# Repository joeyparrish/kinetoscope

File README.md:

<h1>
  <picture>
    <source media="(prefers-color-scheme: dark)" srcset="logo-dark.svg">
    <source media="(prefers-color-scheme: light)" srcset="logo.svg">
    
  </picture>
</h1>

A Sega Genesis / Mega Drive Streaming Video Player

## Overview

Kinetoscope can either play video embedded in a standard ROM, or it can stream
video over WiFi using special hardware in a custom cartridge.  It uses a custom
video format detailed in
[`software/player/inc/segavideo_format.h`](software/player/inc/segavideo_format.h)
and encoded by
[`encoder/encode_sega_video.py`](encoder/encode_sega_video.py).

Kinetoscope takes its name from the [first moving picture
device](https://www.britannica.com/technology/Kinetoscope), invented in 1891 by
Thomas Edison and William Dickson.  While the 1891 original Kinetoscope was
able to display 46 frames per second, this project for a 1988 game console can
only push 10.

The default format is displayed at ~320x240p analog SD resolution at 10fps,
with 8-bit PCM audio at 13kHz.  The encoded pixels are not square.  The encoded
frames use a 256x224 resolution due to hardware limitations, and are displayed
at a different ratio by the Sega's Video Display Processor (VDP).

If video is embedded in the ROM, you can only fit about 13.6 seconds in a 4MB
cartridge/ROM.

For streaming, an RLE compression scheme is used to reduce required throughput,
and the microcontroller decompresses the video into SRAM on the fly.

Schematics and board layouts for special streaming hardware can be found in the
[`hardware/`](hardware/) folder.

You can download a pre-built emulator for macOS, Windows, or Linux from the
[releases page](https://github.com/joeyparrish/kinetoscope/releases).
(**NOTE:** On Linux, you should have OpenGL and PulseAudio pre-installed to use
these binaries.)

## Web Demo

To see Kinetoscope in a web-based emulator, check out
[https://joeyparrish.github.io/kinetoscope/](https://joeyparrish.github.io/kinetoscope/)

## Prototype

The first working prototype of the hardware was a stack of boards that looked
like this:

## Presentation

 - [Video presentation](https://youtu.be/0Atlf_whVgA)
 - [Presentation slides](https://docs.google.com/presentation/d/1nqJEwOmjEmVEMR6anbMV5HIaqYFpPi18ib-LaNSrTQE/)

## Project Folders

Each folder has a README with more information, including prerequisites that
must be installed to work on that part of the project.

 - [`software/`](software/): The player library and sample projects, which run
   on the Sega, written using [SGDK][].
 - [`encoder/`](encoder/): The video encoder, which generates videos in an
   appropriate format for embedding or streaming.
 - [`hardware/`](hardware/): The schematics and board layouts for a custom
   cartridge with special streaming hardware.
 - [`firmware/`](firmware/): The firmware that runs on the microcontroller of
   the custom cartridge hardware.
 - [`emulator-patches/`](emulator-patches/): Patches for OSS emulators to
   emulate the streaming hardware.
 - [`server/`](server/): Details on running a server for Sega video streams.
 - [`canned-videos/`](canned-videos/): Download canned, pre-encoded videos.

## Links

Related Projects:

 - [SGDK][]: A free and open development kit for the Sega Genesis / Mega Drive
 - The logo font is [Kode Mono](https://kodemono.com/)
 - [Sega Genesis Slide Generator and Viewer](https://github.com/joeyparrish/sega-slides/)
 - [Krikzz](https://krikzz.com/our-products/cartridges/): Incredible hardware
   for retro game console hacking and development, including flash carts

Socials:

 - [LinkedIn](https://www.linkedin.com/in/joeyparrish/)
 - [Video-Dev Slack](https://www.video-dev.org/)
 - [Pokemon Go](https://joeyparrish.github.io/joeyparrish/logos/trainer-code.png)
 - End of list

[SGDK]: https://github.com/Stephane-D/SGDK

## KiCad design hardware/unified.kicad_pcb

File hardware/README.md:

# Kinetoscope Hardware Design

The hardware is composed of several stacking boards, each of which hosts a set
of subcomponents.  The subcomponents are each in a subsheet, exposing
hierarchical pins and buses to the parent sheet.

One of these boards includes a microcontroller with WiFi, and runs its own
firmware to take commands from the Sega ROM.  See firmware in the
`../firmware/` folder.

## Prototype

The first working prototype looked like this:

## Prerequisites

The hardware design was done in KiCad 9, and routing was done in FreeRouting.
To install KiCad 9 and FreeRouting on Ubuntu, run:

```sh
sudo add-apt-repository --yes ppa:kicad/kicad-9.0-releases
sudo apt update
sudo apt install --install-recommends kicad default-jre wget unzip
wget https://github.com/freerouting/freerouting/releases/download/v1.9.0/freerouting-1.9.0-linux-x64.zip
sudo unzip -j -d /opt/freerouting freerouting-1.9.0-linux-x64.zip freerouting-1.9.0-linux-x64/lib/app/freerouting-executable.jar
```

To see hardware schematics without KiCad, open the PDF files in the
[`hardware/`](hardware/) folder.

To order boards, see hardware zip files attached to
[releases](https://github.com/joeyparrish/kinetoscope/releases).  These can be
uploaded to JLCPCB.

TODO: Document ordering process

## Boards

The stacking boards are:
 - `cart`: Cartridge Board
   - This is the board that actually plugs into the Sega Genesis.
   - It has 2MB of flash, which acts as the "ROM" chip for addresses 0-2MB, and
     contains the code that runs on the Sega.
   - The flash chip is compatible with the [Krikzz FlashKit Programmer MD][].
   - There is also a pin header on top that the other boards stack onto.
   - The pin header could also be used as a kind of breakout board for the
     development of other Sega cartridge projects.
   - Right-angle pin headers on the sides of the board are optional, and used
     only for debugging.
   - When ordering this through JLCPCB:
     - Be sure to set the following options:
       - Surface Finish: ENIG
       - Gold Fingers: Yes
       - 30°finger chamfered: Yes
     - The following parts will not be properly placed by JLCPCB's systems
       automatically, and must be adjusted manually during the ordering process:
       - J1 (pin header for attaching other boards, wrong location and rotation)
       - U2 (voltage regulator, offset a little too far to the right)
     - The following optional parts _may_ be populated by hand if you wish:
       - J4 (2-pin right-angle header for measuring current)
 - `sram-bank`: SRAM Bank Board
   - There are actually two of these in the stack, one for each 1MB SRAM bank.
   - These host the SRAM itself, and the buffers that allow it to be
     alternately controlled by the Sega or the microcontroller.  This is the
     most complex.  Two solder jumpers on the board select whether it responds
     as bank 0 or bank 1.
   - When ordering this through JLCPCB:
     - The following parts could easily be populated by hand if you wish:
       - J1 & J2 (stacking headers, 2x26 and 2x21 pins respectively)
     - The following **must** be soldered by hand:
       - JP1 and JP2 are solder jumpers that must be closed on each board; to
         set bank 0, bridge center to left on both jumpers; to set bank 1,
         bridge center to right on both jumpers (also indicated on silkscreen)
 - `microcontroller`: Microcontroller Board
   - This hosts the microcontroller, registers, sync token, and buffers to send
     data to SRAM.
   - The registers and sync token allow the Sega to send commands to the
     microcontroller and wait for responses.
   - The microcontroller is a Raspberry Pi Pico W, which receives commands
     through the registers and sync token, and is responsible for WiFi/Ethernet
     and streaming video to SRAM.  You can buy one here for $7 (as of September
     2024): https://www.adafruit.com/product/5544
   - When ordering this through JLCPCB:
     - The following parts may not be properly rendered by JLCPCB's systems
       automatically.  You may choose to leave them off your order and populate
       them by hand if you wish:
       - J3 and J4 are 20-pin female headers @ 0.1 inch pitch, to mount a
         Raspberry Pi Pico W with male headers facing down
     - The following parts could easily be populated by hand if you wish:
       - J1 & J2 (stacking headers, 2x26 and 2x21 pins respectively)
       - J6 (optional 2x3 female header to connect to an Ethernet Adapter Board
         with an [Adafruit Ethernet Featherwing][])
     - The following **must** be done by hand:
       - A single jumper must be added to either J5 or J7 (see silkscreen notes
         for play vs programming setting)
 - `ethernet`: Ethernet Adapter Board
   - This connects to an optional header on the microcontroller board and
     allows you to plug in the [Adafruit Ethernet Featherwing][].
   - If Ethernet is connected, the firmware prefers Ethernet over WiFi.
   - When ordering this through JLCPCB:
     - All headers could easily be populated by hand if you wish to skip paid
       assembly:
       - J1 & J2 (female headers on top of the board, 1x16 and 1x12
         respectively, where the Featherwing plugs in)
     - The following **must** be done by hand, because JLCPCB will only
       populate one side of the board:
       - J3 (male header on the bottom of the board, where it attaches to the
         Microcontroller Board)

## Sheets

The subsheets are:
 - `address-counter-internal`: SRAM address counter
   - The microcontroller doesn't have enough pins to output the SRAM address it
     wants to write to, so instead, this counter is used to generate sequential
     addresses.
 - `buffer-16-internal`: 16-bit tri-state, level-shifting buffer
   - This buffer allows us to manage control of the 16-bit data bus on the
     SRAM, switching between Sega and microcontroller control when needed.
 - `buffer-22-internal`: 22-bit tri-state, level-shifting buffer
   - This buffer allows us to manage control of the 19-bit address bus and
     control signals on the SRAM, switching between Sega and microcontroller
     control when needed.
 - `data-register-internal`: 16-bit serial-to-parallel shift register
   - The microcontroller doesn't have enough pins to output the SRAM words it
     wants to write, so instead, this register is used to convert a serial
     output from the microcontroller into the parallel input needed by the
     SRAM.
 - `flash-internal`: Flash connected to buses
   - Flash memory connected to buses to simplify top-level schematics.
 - `kinetoscope-header-internal`: Kinetoscope stacking pin headers
   - The stacking pin headers used for inter-board signals.
 - `register-file-internal`: 4x 8-bit Register File
   - Special registers the Sega writes to and the microcontroller reads from to
     receive commands.
 - `sram-internal`: SRAM connected to buses
   - SRAM connected to buses to simplify top-level schematics.
 - `sync-token-internal`: Shared Sync Token
   - A pair of single bit tokens.  One can be set by the Sega and cleared by
     the microcontroller, and the other vice-versa.  Both CPUs can read the
     state of both tokens.  For the command bit, the Sega sets it to tell the
     microcontroller that a command has been written to the registers. The
     microcontroller clears it when the command has been completed.  For the
     error bit, the microcontroller sets it to tell the Sega that an error has
     occurred, and the Sega clears it after the error has been read.

## Routing

To reroute a PCB after modifying the schematic:

  1. Open the PCB in KiCad
  2. Select all (CTRL+A)
  3. Right click the board, "Select >", "Filter Selected Items..."
  4. Uncheck "All items"
  5. Check "Include tracks" and "Include vias"
  6. Delete (Delete key)
  7. Update PCB from schematic (F8)
  8. Click "Update PCB", then "Close"
  9. Save PCB (CTRL+S)
  10. Select "File", "Export >", "Specctra DSN..."
  11. Click "Save" (and "Replace" if prompted)
  12. Run `route-pcb.sh` with the name of the board.  For example:

```sh
./route-pcb.sh sram-bank
```

After the routing process completes:

  1. Open the PCB in KiCad
  2. Select "File", "Import >", "Specctra Session..."
  3. Select the .ses file corresponding to this design
  4. Click "Open"
  5. Redo fill zones (B)
  6. Select "Inspect", "Design Rules Checker"
  7. Click "Run DRC"
  8. Manually fix any violations or unconnected items

## Programming

To program the Flash chip in-place:
 1. Insert the cartridge board into the [Krikzz FlashKit Programmer MD][]
 2. Write to it as you would a normal flash cart, using the
    [original FlashKit-MD software][] (GUI) or [FlashKit MD Python Client][]
    (command line)

[Krikzz FlashKit Programmer MD]: https://krikzz.com/our-products/accessories/flashkitmd.html
[original FlashKit-MD software]: https://krikzz.com/pub/support/flashkit-md/
[FlashKit MD Python Client]: https://github.com/joeyparrish/flashkit-md-py
[Adafruit Ethernet Featherwing]: https://www.adafruit.com/product/3201

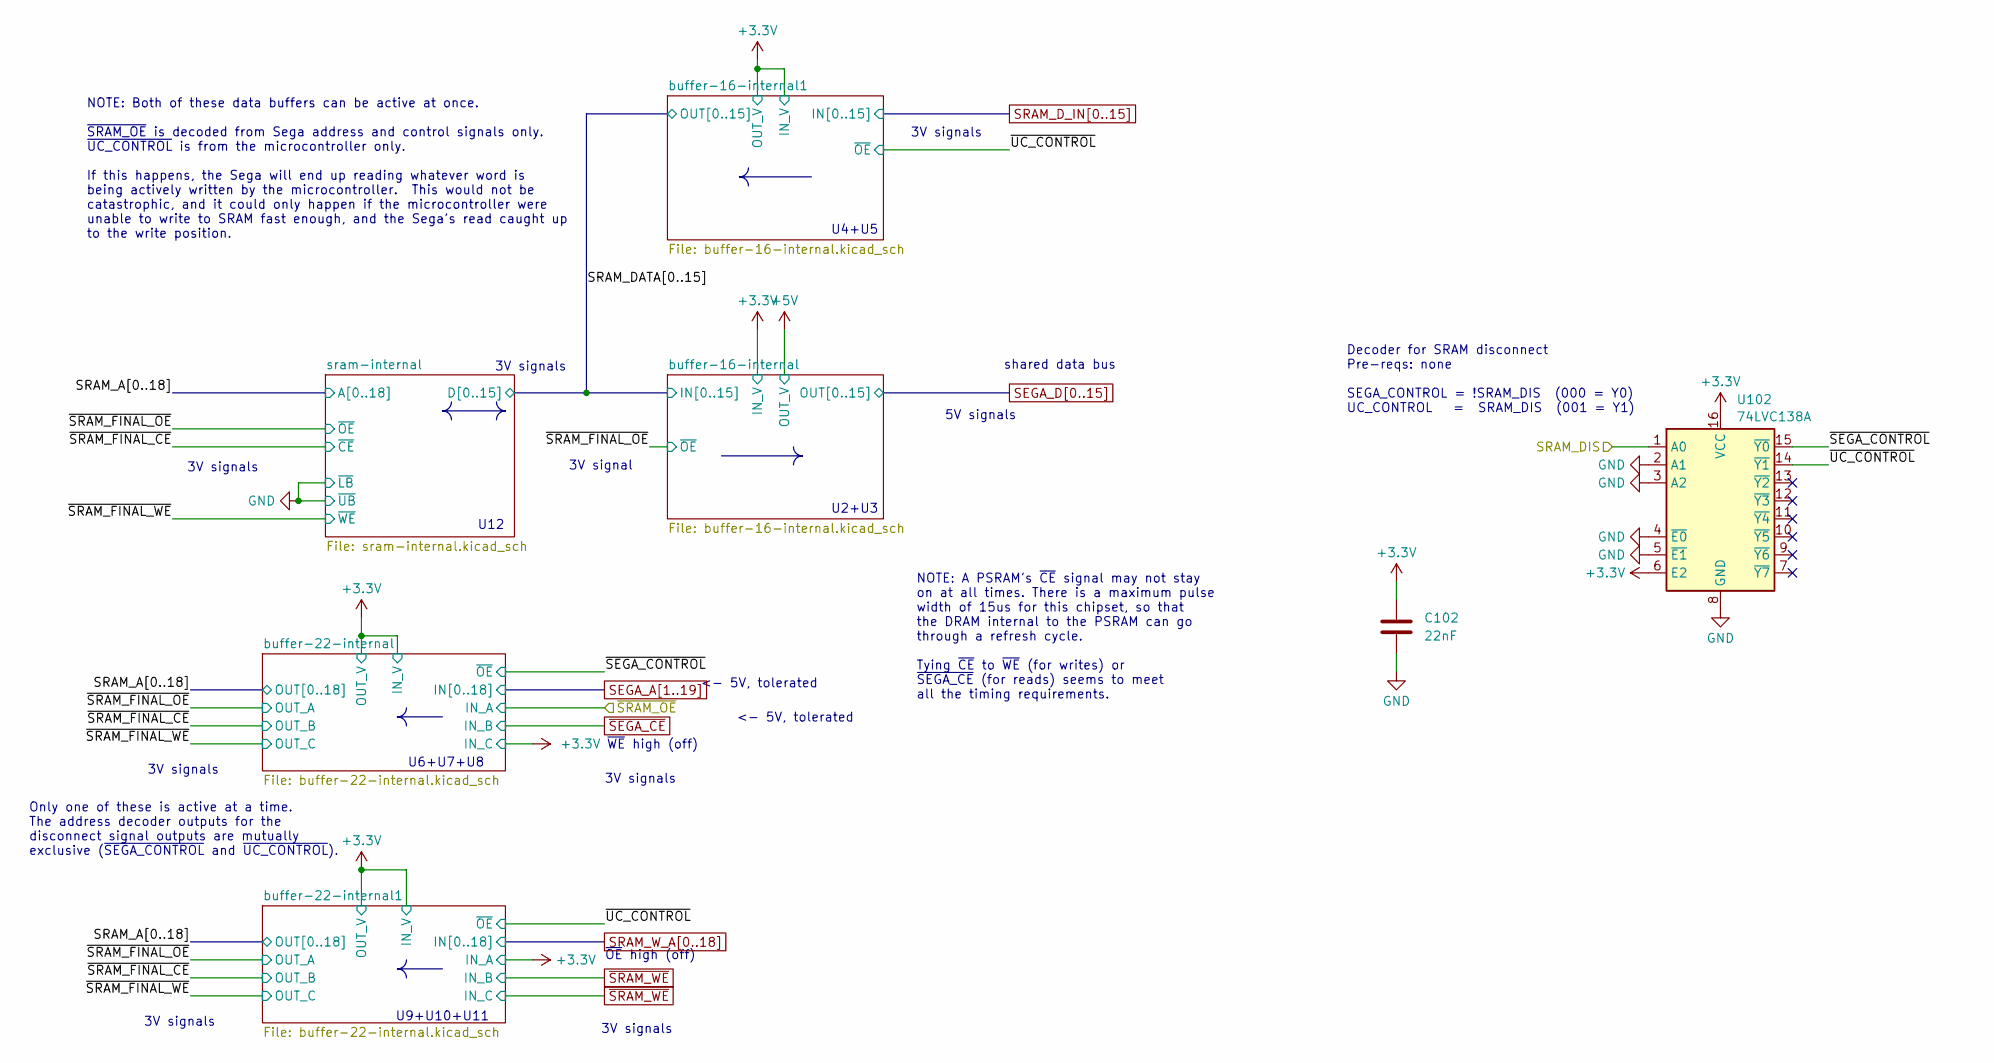
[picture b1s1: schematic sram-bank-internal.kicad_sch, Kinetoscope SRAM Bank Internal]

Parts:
C102: 22nF; C_0603_1608Metric; Mouser Part Number 80-C0603C223K4R; JLCPCB Part Number CL10B223KB8NNNC
U102: 74LVC138A; TSSOP-16_4.4x5mm_P0.65mm; Mouser Part Number 771-74LVC138APW-T; JLCPCB Part Number C6062

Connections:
+3.3V: C102.1, U102.6 (E2), U102.16 (VCC); also elsewhere on the board
/sram-bank-internal/~SEGA_CONTROL: U102.15 (~Y0); also elsewhere on the board
/sram-bank-internal/~UC_CONTROL: U102.14 (~Y1); also elsewhere on the board
GND: C102.2, U102.2 (A1), U102.3 (A2), U102.4 (~E0), U102.5 (~E1), U102.8 (GND); also elsewhere on the board
SRAM_DIS_0: U102.1 (A0); also elsewhere on the board

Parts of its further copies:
C201: 22nF; C_0603_1608Metric; Mouser Part Number 80-C0603C223K4R; JLCPCB Part Number CL10B223KB8NNNC
U201: 74LVC138A; TSSOP-16_4.4x5mm_P0.65mm; Mouser Part Number 771-74LVC138APW-T; JLCPCB Part Number C6062

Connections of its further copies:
+3.3V: C201.1, U201.6 (E2), U201.16 (VCC); also elsewhere on the board
/sram-bank-internal1/~SEGA_CONTROL: U201.15 (~Y0); also elsewhere on the board
/sram-bank-internal1/~UC_CONTROL: U201.14 (~Y1); also elsewhere on the board
GND: C201.2, U201.2 (A1), U201.3 (A2), U201.4 (~E0), U201.5 (~E1), U201.8 (GND); also elsewhere on the board
SRAM_DIS_1: U201.1 (A0); also elsewhere on the board

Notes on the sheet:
5V signals
U6+U7+U8
3V signals
U9+U10+U11
<- 5V, tolerated
U4+U5
U12
shared data bus
3V signal
Decoder for SRAM disconnect Pre-reqs: none SEGA_CONTROL = !SRAM_DIS (000 = Y0) UC_CONTROL = SRAM_DIS (001 = Y1)
NOTE: A PSRAM's ~{CE} signal may not stay on at all times. There is a maximum pulse width of 15us for this chipset, so that the DRAM internal to the PSRAM can go through a refresh cycle. Tying ~{CE} to ~{WE} (for writes) or ~{SEGA_CE} (for reads) seems to meet all the timing requirements.
~{OE} high (off)
U2+U3
Only one of these is active at a time. The address decoder outputs for the disconnect signal outputs are mutually exclusive (~{SEGA_CONTROL} and ~{UC_CONTROL}).
~{WE} high (off)
NOTE: Both of these data buffers can be active at once. ~{SRAM_OE} is decoded from Sega address and control signals only. ~{UC_CONTROL} is from the microcontroller only. If this happens, the Sega will end up reading whatever word is being actively written by the microcontroller. This would not be c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

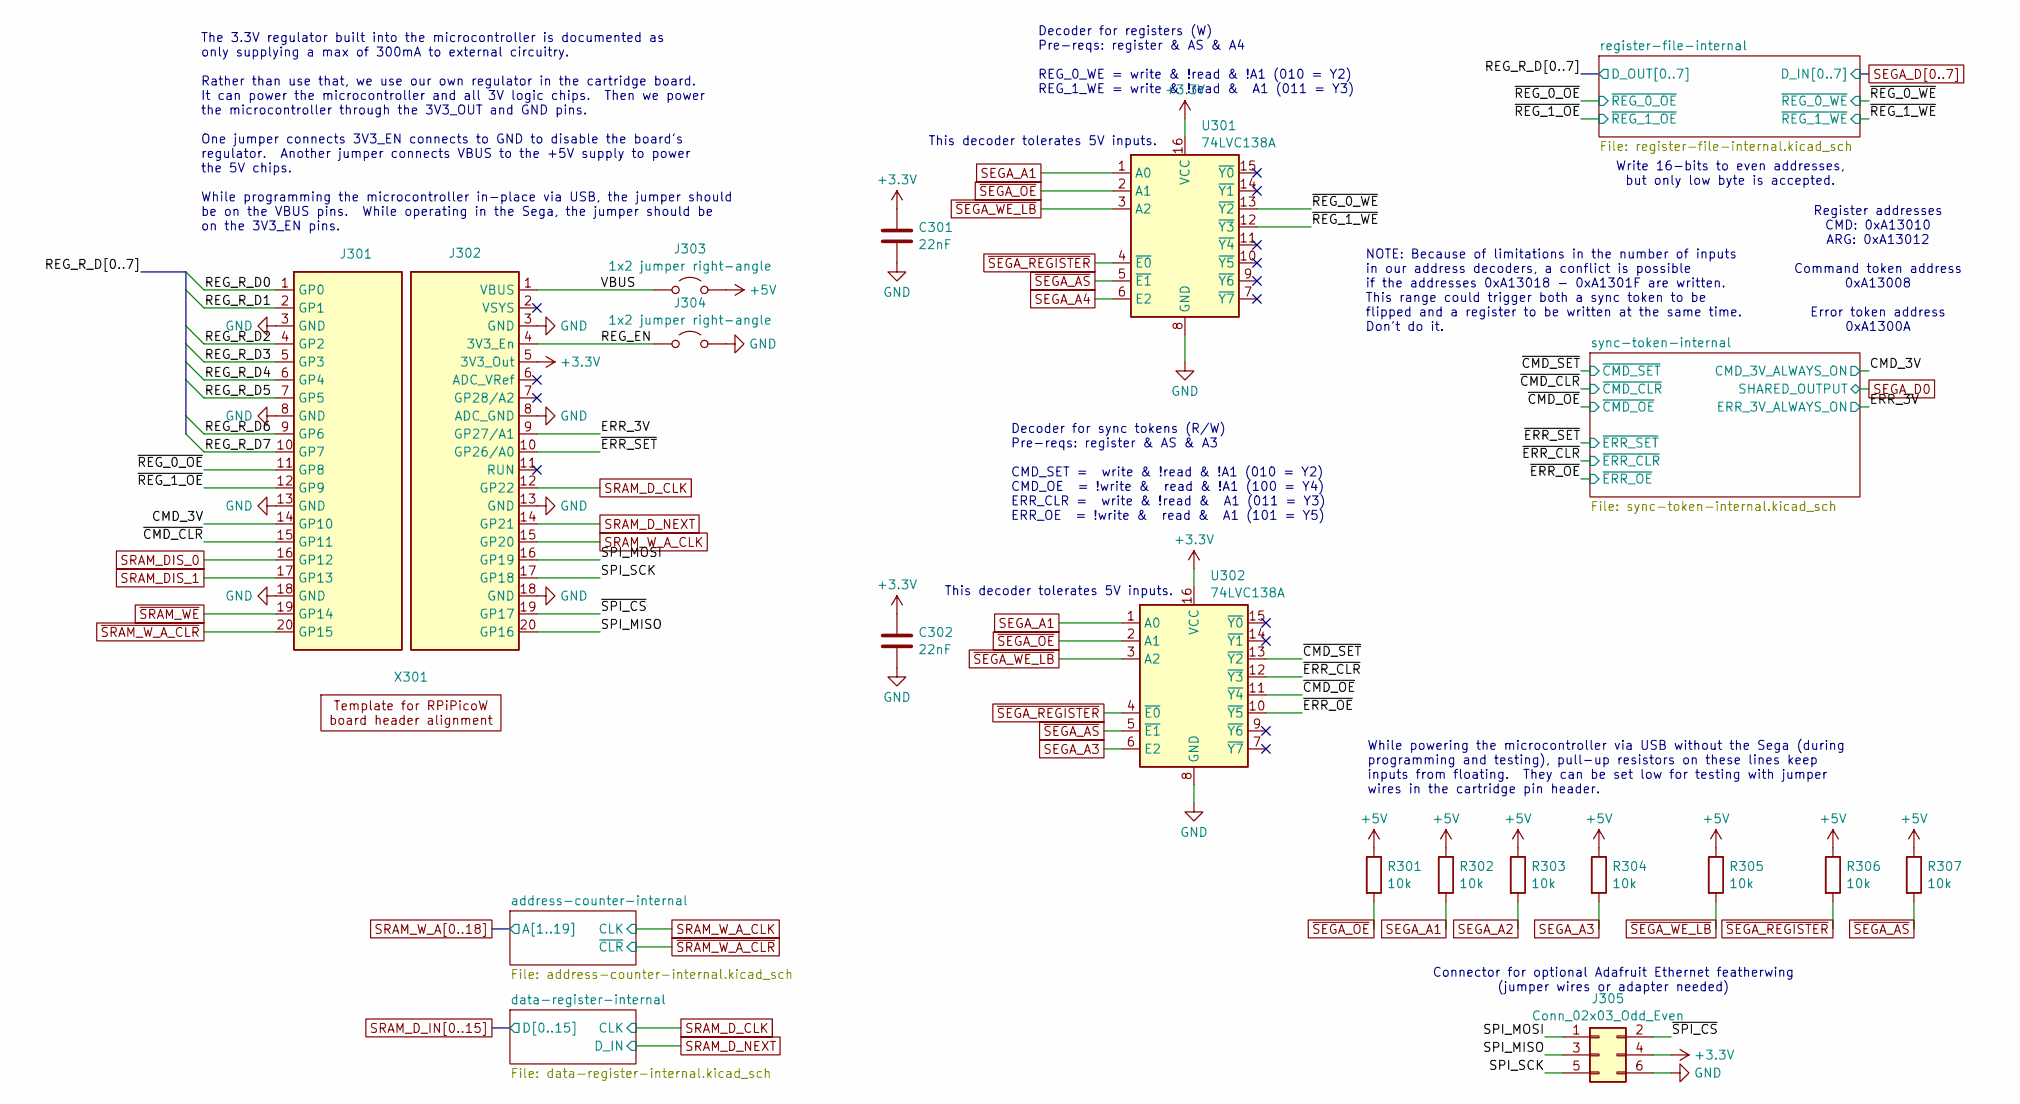
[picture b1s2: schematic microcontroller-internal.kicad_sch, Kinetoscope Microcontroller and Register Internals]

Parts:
C301, C302: 22nF; C_0603_1608Metric; Mouser Part Number 187-CL10B223KB8NNNC
J301, J302: PinHeader_1x20_P2.54mm_Vertical; Mouser Part Number 710-61302011821; JLCPCB Part Number C5224030
J303, J304: 1x2 jumper right-angle; PinHeader_1x02_P2.54mm_Horizontal; Mouser Part Number 737-PH1RB-02-UA; JLCPCB Part Number C6952593
J305: Conn_02x03_Odd_Even; PinHeader_2x03_P2.54mm_Vertical; Mouser Part Number 710-61300621821; JLCPCB Part Number C4944863
R301, R302, R303, R304, R305, R306, R307: 10k; R_0603_1608Metric; Part Number RT0603DRD0710KL; JLCPCB Part Number C136944
U301, U302: 74LVC138A; TSSOP-16_4.4x5mm_P0.65mm; Mouser Part Number 771-74LVC138APW-T
X301: Raspberry_Pi_Pico_W_template

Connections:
+3.3V: C301.1, C302.1, J302.5 (3V3_Out), J305.4, U301.16 (VCC), U302.16 (VCC); also elsewhere on the board
+5V: J303.2 (B), R301.1, R302.1, R303.1, R304.1, R305.1, R306.1, R307.1; also elsewhere on the board
/microcontroller-internal/CMD_3V: J301.14 (GP10); also elsewhere on the board
/microcontroller-internal/ERR_3V: J302.9 (GP27/A1); also elsewhere on the board
/microcontroller-internal/REG_EN: J302.4 (3V3_En), J304.1 (A)
/microcontroller-internal/REG_R_D0: J301.1 (GP0); also elsewhere on the board
/microcontroller-internal/REG_R_D1: J301.2 (GP1); also elsewhere on the board
/microcontroller-internal/REG_R_D2: J301.4 (GP2); also elsewhere on the board
/microcontroller-internal/REG_R_D3: J301.5 (GP3); also elsewhere on the board
/microcontroller-internal/REG_R_D4: J301.6 (GP4); also elsewhere on the board
/microcontroller-internal/REG_R_D5: J301.7 (GP5); also elsewhere on the board
/microcontroller-internal/REG_R_D6: J301.9 (GP6); also elsewhere on the board
/microcontroller-internal/REG_R_D7: J301.10 (GP7); also elsewhere on the board
/microcontroller-internal/SPI_MISO: J302.20 (GP16), J305.3
/microcontroller-internal/SPI_MOSI: J302.16 (GP19), J305.1
/microcontroller-internal/SPI_SCK: J302.17 (GP18), J305.5
/microcontroller-internal/VBUS: J302.1 (VBUS), J303.1 (A)
/microcontroller-internal/~CMD_CLR: J301.15 (GP11); also elsewhere on the board
/microcontroller-internal/~CMD_OE: U302.11 (~Y4); also elsewhere on the board
/microcontroller-internal/~CMD_SET: U302.13 (~Y2); also elsewhere on the board
/microcontroller-internal/~ERR_CLR: U302.12 (~Y3); also elsewhere on the board
/microcontroller-internal/~ERR_OE: U302.10 (~Y5); also elsewhere on the board
/microcontroller-internal/~ERR_SET: J302.10 (GP26/A0); also elsewhere on the board
/microcontroller-internal/~REG_0_OE: J301.11 (GP8); also elsewhere on the board
/microcontroller-internal/~REG_0_WE: U301.13 (~Y2); also elsewhere on the board
/microcontroller-internal/~REG_1_OE: J301.12 (GP9); also elsewhere on the board
/microcontroller-internal/~REG_1_WE: U301.12 (~Y3); also elsewhere on the board
/microcontroller-internal/~SPI_CS: J302.19 (GP17), J305.2
GND: C301.2, C302.2, J301.3 (GND), J301.8 (GND), J301.13 (GND), J301.18 (GND), J302.3 (GND), J302.8 (ADC_GND), J302.13 (GND), J302.18 (GND), J304.2 (B), J305.6, U301.8 (GND), U302.8 (GND); also elsewhere on the board
SEGA_A1: R302.2, U301.1 (A0), U302.1 (A0); also elsewhere on the board
SEGA_A2: R303.2; also elsewhere on the board
SEGA_A3: R304.2, U302.6 (E2); also elsewhere on the board
SEGA_A4: U301.6 (E2); also elsewhere on the board
SRAM_DIS_0: J301.16 (GP12); also elsewhere on the board
SRAM_DIS_1: J301.17 (GP13); also elsewhere on the board
SRAM_D_CLK: J302.12 (GP22); also elsewhere on the board
SRAM_D_NEXT: J302.14 (GP21); also elsewhere on the board
SRAM_W_A_CLK: J302.15 (GP20); also elsewhere on the board
~SEGA_AS: R307.2, U301.5 (~E1), U302.5 (~E1); also elsewhere on the board
~SEGA_OE: R301.2, U301.2 (A1), U302.2 (A1); also elsewhere on the board
~SEGA_REGISTER: R306.2, U301.4 (~E0), U302.4 (~E0); also elsewhere on the board
~SEGA_WE_LB: R305.2, U301.3 (A2), U302.3 (A2); also elsewhere on the board
~SRAM_WE: J301.19 (GP14); also elsewhere on the board
~SRAM_W_A_CLR: J301.20 (GP15); also elsewhere on the board

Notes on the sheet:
This decoder tolerates 5V inputs.
While powering the microcontroller via USB without the Sega (during programming and testing), pull-up resistors on these lines keep inputs from floating. They can be set low for testing with jumper wires in the cartridge pin header.
The 3.3V regulator built into the microcontroller is documented as only supplying a max of 300mA to external circuitry. Rather than use that, we use our own regulator in the cartridge board. It can power the microcontroller and all 3V logic chips. Then we power the microcontroller through the 3V3_O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
Write 16-bits to even addresses, but only low byte is accepted.
Register addresses CMD: 0xA13010 ARG: 0xA13012 Command token address 0xA13008 Error token address 0xA1300A
Decoder for registers (W) Pre-reqs: register & AS & A4 REG_0_WE = write & !read & !A1 (010 = Y2) REG_1_WE = write & !read & A1 (011 = Y3)
Connector for optional Adafruit Ethernet featherwing (jumper wires or adapter needed)
NOTE: Because of limitations in the number of inputs in our address decoders, a conflict is possible if the addresses 0xA13018 - 0xA1301F are written. This range could trigger both a sync token to be flipped and a register to be written at the same time. Don't do it.
Decoder for sync tokens (R/W) Pre-reqs: register & AS & A3 CMD_SET = write & !read & !A1 (010 = Y2) CMD_OE = !write & read & !A1 (100 = Y4) ERR_CLR = write & !read & A1 (011 = Y3) ERR_OE = !write & read & A1 (101 = Y5)

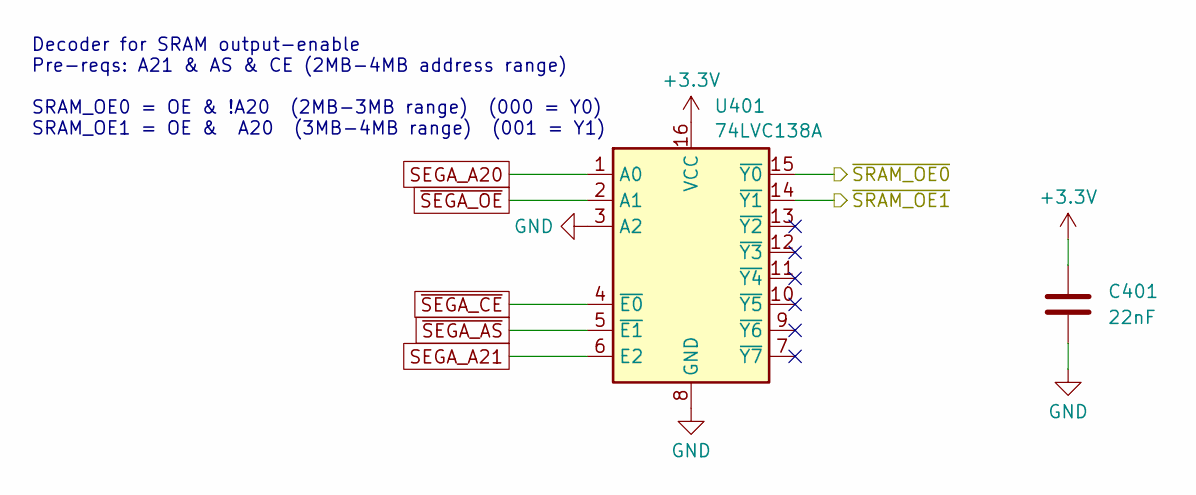
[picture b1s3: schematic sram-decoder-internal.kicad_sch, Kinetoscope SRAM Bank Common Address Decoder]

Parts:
C401: 22nF; C_0603_1608Metric; Mouser Part Number 80-C0603C223K4R; JLCPCB Part Number CL10B223KB8NNNC
U401: 74LVC138A; TSSOP-16_4.4x5mm_P0.65mm; Mouser Part Number 771-74LVC138APW-T; JLCPCB Part Number C6062

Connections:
+3.3V: C401.1, U401.16 (VCC); also elsewhere on the board
/sram-bank-internal1/~SRAM_OE: U401.14 (~Y1); also elsewhere on the board
/sram-bank-internal/~SRAM_OE: U401.15 (~Y0); also elsewhere on the board
GND: C401.2, U401.3 (A2), U401.8 (GND); also elsewhere on the board
SEGA_A20: U401.1 (A0); also elsewhere on the board
SEGA_A21: U401.6 (E2); also elsewhere on the board
~SEGA_AS: U401.5 (~E1); also elsewhere on the board
~SEGA_CE: U401.4 (~E0); also elsewhere on the board
~SEGA_OE: U401.2 (A1); also elsewhere on the board

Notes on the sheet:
Decoder for SRAM output-enable Pre-reqs: A21 & AS & CE (2MB-4MB address range) SRAM_OE0 = OE & !A20 (2MB-3MB range) (000 = Y0) SRAM_OE1 = OE & A20 (3MB-4MB range) (001 = Y1)

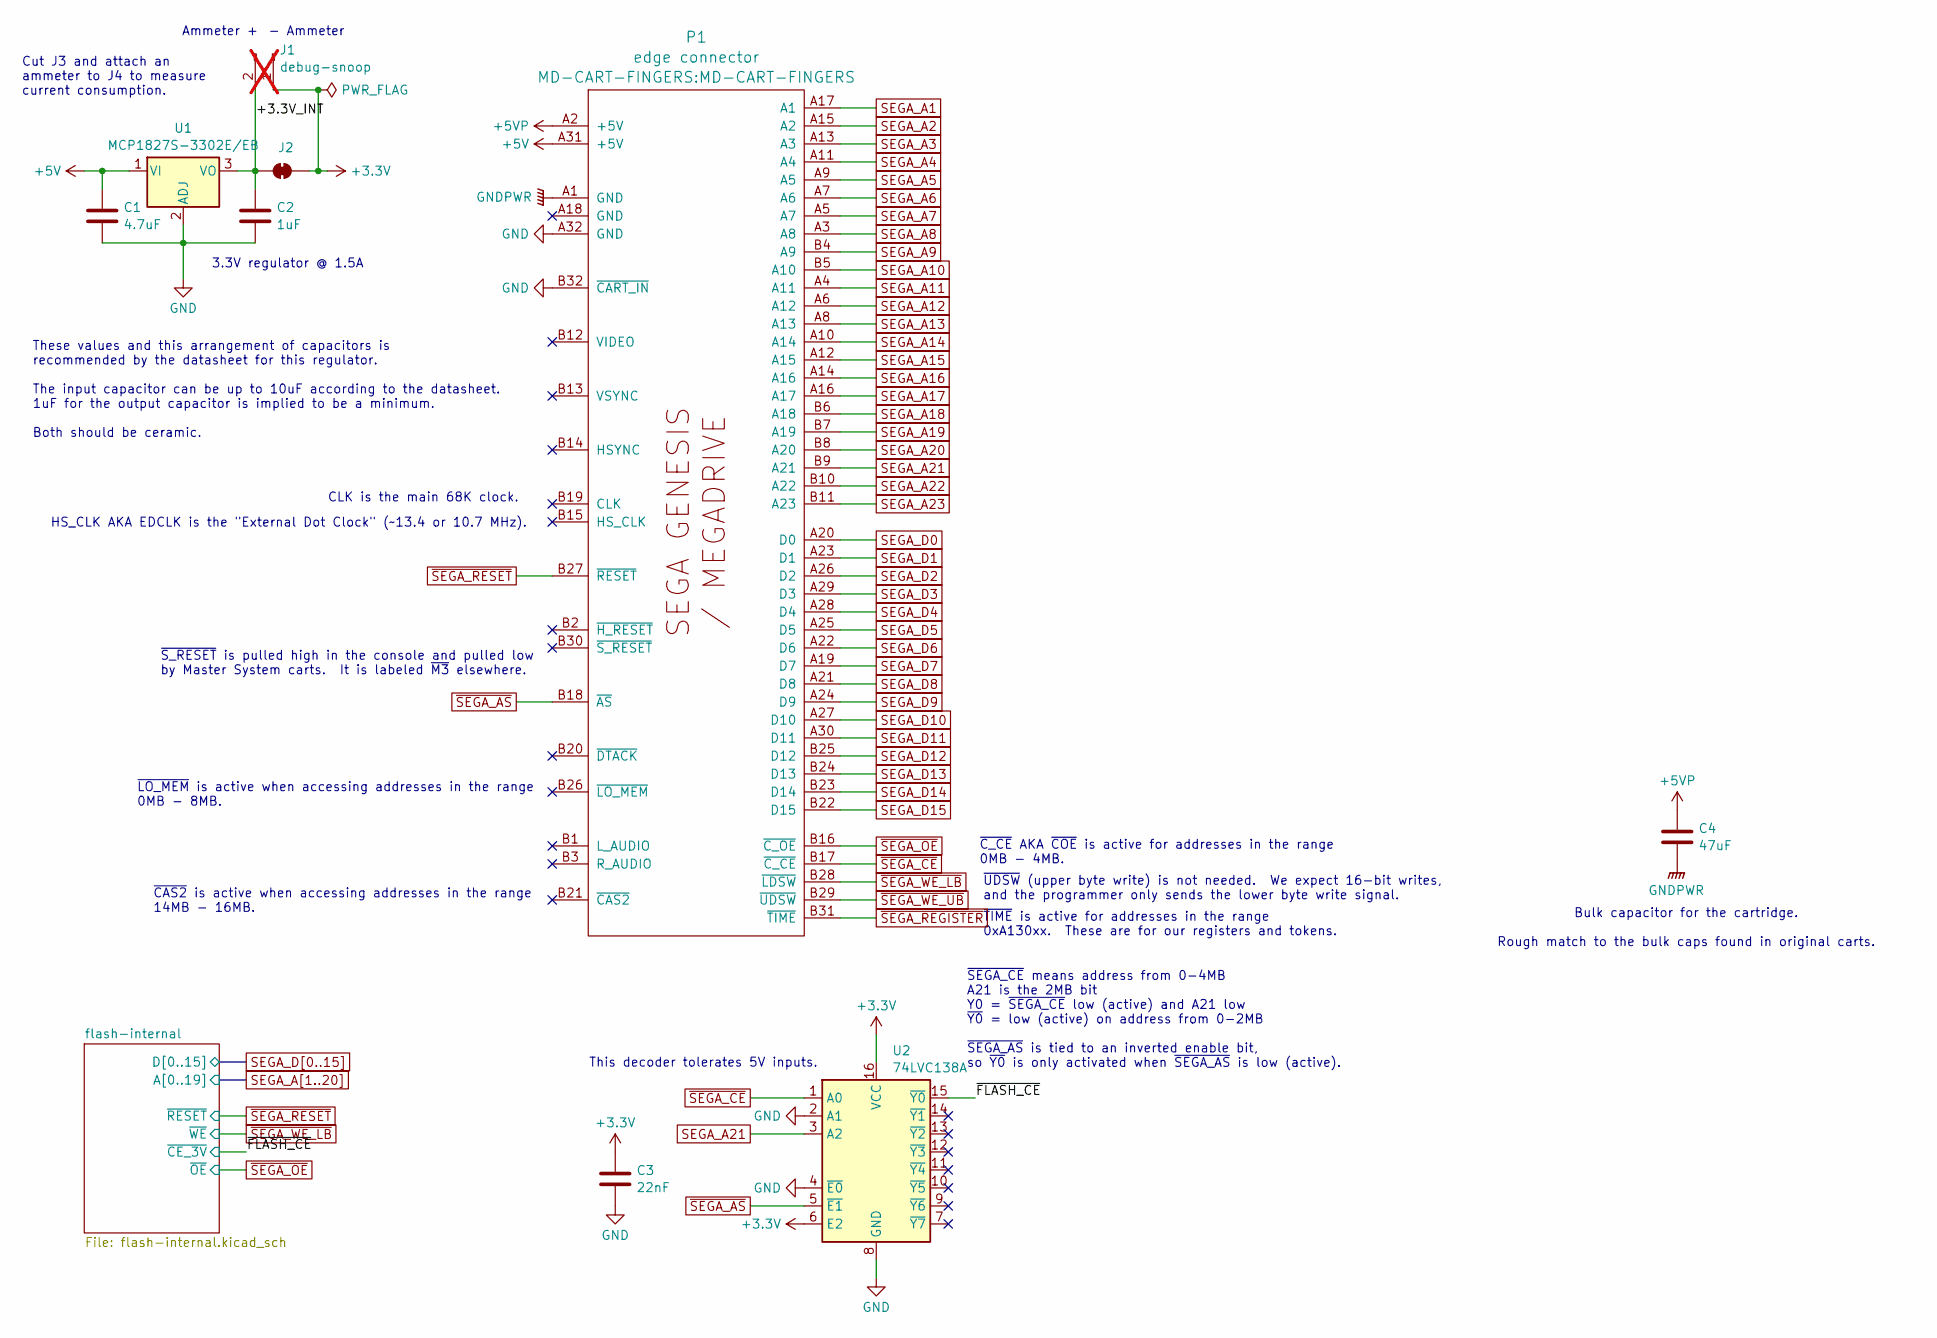
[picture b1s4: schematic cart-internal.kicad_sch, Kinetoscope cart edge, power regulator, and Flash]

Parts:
C1: 4.7uF; C_0603_1608Metric; Mouser Part Number 81-GRM188Z71C475KE1J
C2: 1uF; C_0603_1608Metric; Part Number C0603C105K4RACTU; Mouser Part Number 80-C0603C105K4R
C3: 22nF; C_0603_1608Metric; Mouser Part Number 80-C0603C223K4R
C4: 47uF; C_1206_3216Metric; Mouser Part Number 187-CL31A476MPHNNNE
J1: debug-snoop; PinHeader_1x02_P2.54mm_Horizontal; not fitted
J2: SolderJumper-2_P1.3mm_Bridged_Pad1.0x1.5mm
P1: edge connector; MD-CART-FINGERS
U1: MCP1827S-3302E/EB; TO-252-3_TabPin2; Mouser Part Number 579-MCP1827S3302E/EB
U2: 74LVC138A; TSSOP-16_4.4x5mm_P0.65mm; Mouser Part Number 771-74LVC138APW-T; JLCPCB Part Number C6062

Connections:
+3.3V: C3.1, J1.1, J2.2 (B), U2.6 (E2), U2.16 (VCC); also elsewhere on the board
+5V: C1.1, P1.A31 (+5V), U1.1 (VI); also elsewhere on the board
+5VP: C4.1, P1.A2 (+5V)
/cart-internal/+3.3V_INT: C2.1, J1.2, J2.1 (A), U1.3 (VO)
/cart-internal/~FLASH_CE: U2.15 (~Y0); also elsewhere on the board
GND: C1.2, C2.2, C3.2, P1.A32 (GND), P1.B32 (~CART_IN), U1.2 (ADJ), U2.2 (A1), U2.4 (~E0), U2.8 (GND); also elsewhere on the board
GNDPWR: C4.2, P1.A1 (GND)
SEGA_A1: P1.A17 (A1); also elsewhere on the board
SEGA_A2: P1.A15 (A2); also elsewhere on the board
SEGA_A3: P1.A13 (A3); also elsewhere on the board
SEGA_A4: P1.A11 (A4); also elsewhere on the board
SEGA_A5: P1.A9 (A5); also elsewhere on the board
SEGA_A6: P1.A7 (A6); also elsewhere on the board
SEGA_A7: P1.A5 (A7); also elsewhere on the board
SEGA_A8: P1.A3 (A8); also elsewhere on the board
SEGA_A9: P1.B4 (A9); also elsewhere on the board
SEGA_A10: P1.B5 (A10); also elsewhere on the board
SEGA_A11: P1.A4 (A11); also elsewhere on the board
SEGA_A12: P1.A6 (A12); also elsewhere on the board
SEGA_A13: P1.A8 (A13); also elsewhere on the board
SEGA_A14: P1.A10 (A14); also elsewhere on the board
SEGA_A15: P1.A12 (A15); also elsewhere on the board
SEGA_A16: P1.A14 (A16); also elsewhere on the board
SEGA_A17: P1.A16 (A17); also elsewhere on the board
SEGA_A18: P1.B6 (A18); also elsewhere on the board
SEGA_A19: P1.B7 (A19); also elsewhere on the board
SEGA_A20: P1.B8 (A20); also elsewhere on the board
SEGA_A21: P1.B9 (A21), U2.3 (A2); also elsewhere on the board
SEGA_A22: P1.B10 (A22)
SEGA_A23: P1.B11 (A23)
SEGA_D0: P1.A20 (D0); also elsewhere on the board
SEGA_D1: P1.A23 (D1); also elsewhere on the board
SEGA_D2: P1.A26 (D2); also elsewhere on the board
SEGA_D3: P1.A29 (D3); also elsewhere on the board
SEGA_D4: P1.A28 (D4); also elsewhere on the board
SEGA_D5: P1.A25 (D5); also elsewhere on the board
SEGA_D6: P1.A22 (D6); also elsewhere on the board
SEGA_D7: P1.A19 (D7); also elsewhere on the board
SEGA_D8: P1.A21 (D8); also elsewhere on the board
SEGA_D9: P1.A24 (D9); also elsewhere on the board
SEGA_D10: P1.A27 (D10); also elsewhere on the board
SEGA_D11: P1.A30 (D11); also elsewhere on the board
SEGA_D12: P1.B25 (D12); also elsewhere on the board
SEGA_D13: P1.B24 (D13); also elsewhere on the board
SEGA_D14: P1.B23 (D14); also elsewhere on the board
SEGA_D15: P1.B22 (D15); also elsewhere on the board
~SEGA_AS: P1.B18 (~AS), U2.5 (~E1); also elsewhere on the board
~SEGA_CE: P1.B17 (~C_CE), U2.1 (A0); also elsewhere on the board
~SEGA_OE: P1.B16 (~C_OE); also elsewhere on the board
~SEGA_REGISTER: P1.B31 (~TIME); also elsewhere on the board
~SEGA_RESET: P1.B27 (~RESET); also elsewhere on the board
~SEGA_WE_LB: P1.B28 (~LDSW); also elsewhere on the board
~SEGA_WE_UB: P1.B29 (~UDSW)

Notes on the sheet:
~{S_RESET} is pulled high in the console and pulled low by Master System carts. It is labeled ~{M3} elsewhere.
~{SEGA_CE} means address from 0-4MB A21 is the 2MB bit Y0 = ~{SEGA_CE} low (active) and A21 low ~{Y0} = low (active) on address from 0-2MB ~{SEGA_AS} is tied to an inverted enable bit, so ~{Y0} is only activated when ~{SEGA_AS} is low (active).
Ammeter +
Bulk capacitor for the cartridge. Rough match to the bulk caps found in original carts.
- Ammeter
~{C_CE} AKA ~{COE} is active for addresses in the range 0MB - 4MB.
HS_CLK AKA EDCLK is the "External Dot Clock" (~13.4 or 10.7 MHz).
3.3V regulator @ 1.5A
~{TIME} is active for addresses in the range 0xA130xx. These are for our registers and tokens.
Cut J3 and attach an ammeter to J4 to measure current consumption.
~{LO_MEM} is active when accessing addresses in the range 0MB - 8MB.
These values and this arrangement of capacitors is recommended by the datasheet for this regulator. The input capacitor can be up to 10uF according to the datasheet. 1uF for the output capacitor is implied to be a minimum. Both should be ceramic.
This decoder tolerates 5V inputs.
CLK is the main 68K clock.
~{UDSW} (upper byte write) is not needed. We expect 16-bit writes, and the programmer only sends the lower byte write signal.
~{CAS2} is active when accessing addresses in the range 14MB - 16MB.
